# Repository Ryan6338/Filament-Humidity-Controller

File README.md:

# ESPHome Filament Humidity Controller (P/N 000001)
## Overview
This project is for an ESPHome-based 3D printer filament box. The purpose of the PCB is to automatically control a fan which will drive air through dessicant in a 3D printer filament drybox. Using ESPHome allows for easy configuration & automation customization through ESPHome and Home Assistant. It also allows for notifications to be configured when the dessicant has been depleted. The PCB is powered from a USB-C port requiring a 5V, 1A capable USB source. The USB port can be used for flashing the onboard ESP, although after ESPHome firmware has been installed, over the air updates can be used instead.

## File Layout
### [KiCAD](KiCAD/)
The KiCAD folder contains the entire KiCAD project. This can be used to modify the board.
### [Manufacturing Documents](Manufacturing%20Documents/)
The manufacturing documents contains all output files of the KiCAD project. These files fully define the finished PCB. The main document is 000001.pdf. This file has notes defining the other files.
### [Calculations](Calculations/)
Calculations & design criteria can be found in the calculations folder. SMath (.sm) files are used to generate the output files in this folder (.pdf).
### [Simulations](Simulations/)
The simulations folder contains LTSpice simulations generated during the project.
## Board Architecture
A block diagram of the board architecture is pictured below. Each block in the diagram is described in this section.

### USB-C Connector
The board takes in power from the USB-C connector and runs it to both a 12V boost converter and 3.3V linear regulator. The CC pins are used by the upstream device to communicate how much power can be supplied.
### 12V Boost Converter
The 12V boost converter receives 5V (4.75-5.25V) from the USB-C connector & converts it into 12V for the fan. The boost converter is only active when the enable signal is triggered by the ESP32.
### 3.3V Linear Regulator
The 3.3V linear regulator receives 5V from the USB-C connector and regulates it to 3.3V for the humidity sensor & ESP32.
### Humidity Sensor
The humidity sensor receives 3.3V from the linear regulator & is an I2C slave device on the I2C bus connected to the ESP32.
### ESP32
The ESP32 runs ESPHome firmware with a driver to perform fan control with speed feedback & to receive humidity sensor data. Using the custom humidity sensor & fan drivers, the firmware for the ESP32 can be generated using a standard ESPHome yaml file. The ESP32 interfaces with an ESPHome server allowing for easy configuration of control parameters. Upon power on, the ESP32 reads the voltage of the CC pins to ensure adequate power is available from the USB supply prior to enabling the boost converter.
### Fan Connector
The fan connector is a standard 4-Pin computer fan connector which can be used with any 12V computer fan which has a maximum current draw of 200mA or less.
## TODO
1. Write custom ESPHome driver.
2. Create example yaml for ESPHome using custom driver.
3. Design PCB bracket, fan housing & dessicant holder.
## Future Improvements
To make this product consumer-ready, the following improvements should be considered:
1. Add fuse to 5V input.
2. Add ESD protection on USB & fan connectors.

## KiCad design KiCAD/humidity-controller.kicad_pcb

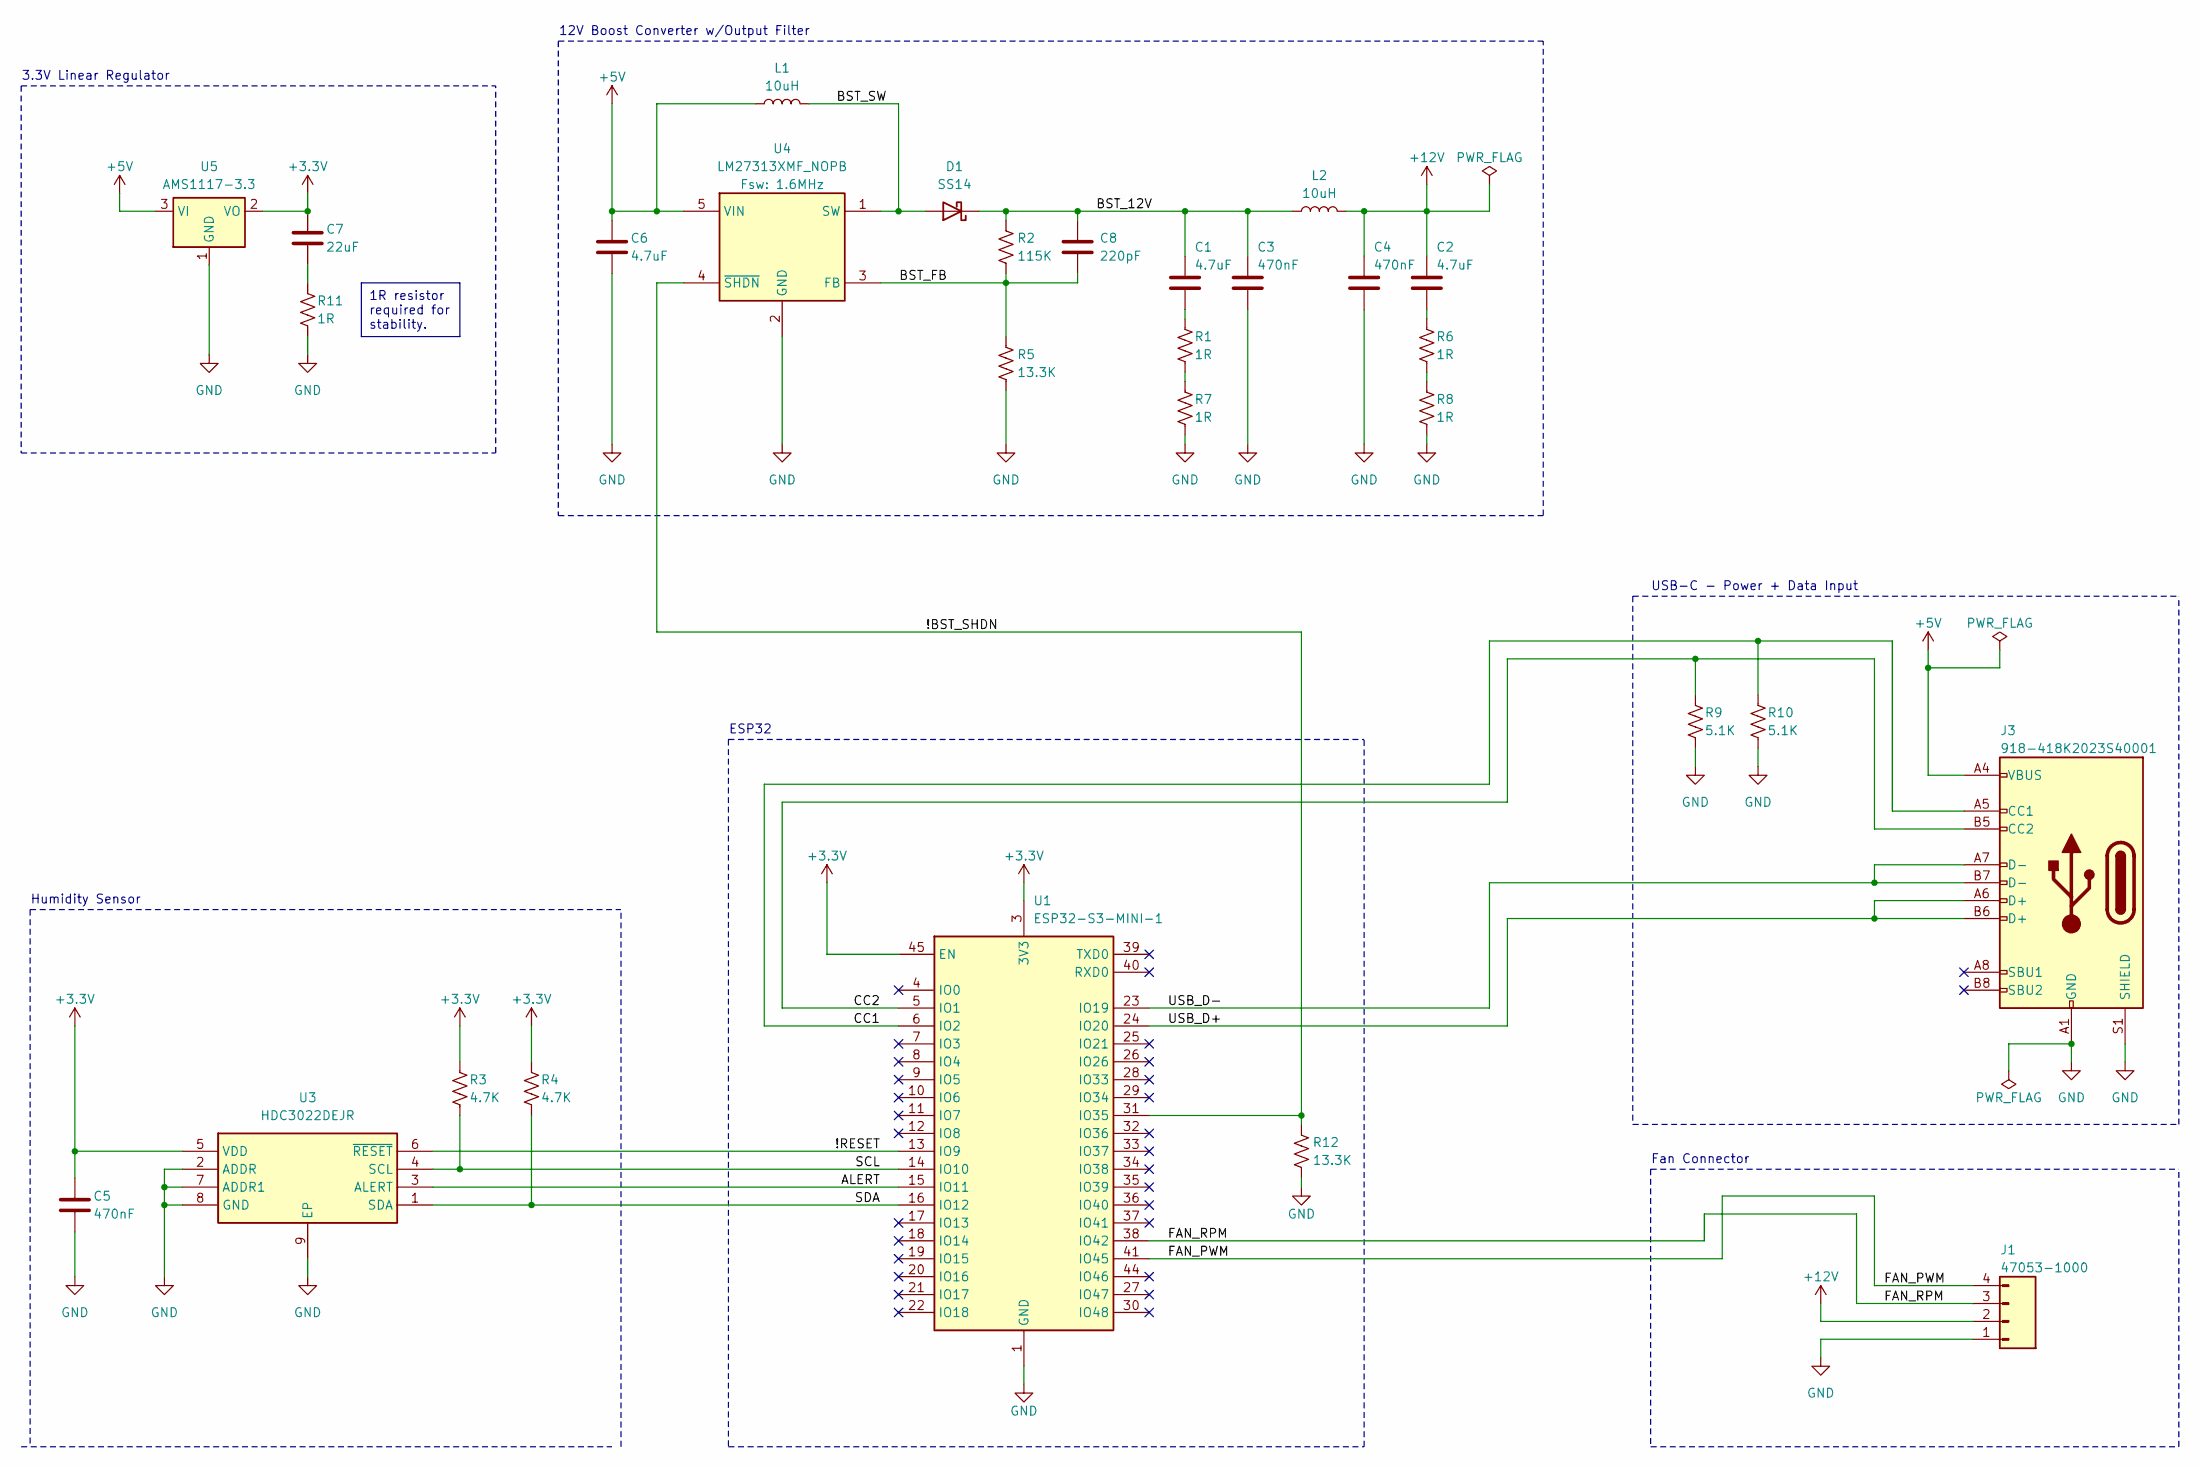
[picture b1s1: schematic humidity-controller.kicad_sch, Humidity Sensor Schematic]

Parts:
C1, C2, C6: 4.7uF; C_1206_3216Metric; MPN 1206B475K500NT; JLCPCB Part # C29823
C3, C4, C5: 470nF; C_0603_1608Metric; MPN CL10B474KA8NNNC; JLCPCB Part # C1623
C7: 22uF; C_0603_1608Metric; MPN CL10A226MQ8NRNC; JLCPCB Part # C59461
C8: 220pF; C_0402_1005Metric; MPN 0402B221K500NT; JLCPCB Part # C1530
D1: SS14; D_SMA; MPN MDD(Microdiode Semiconductor); JLCPCB Part # C2480
J1: Conn_01x04_Pin; 470531000; MPN 47053-1000; JLCPCB Part # C240840
J3: 918-418K2023S40001; USB_C_Receptacle_GCT_USB4105-xx-A_16P_TopMnt_Horizontal; MPN 918-418K2023S40001; JLCPCB Part # C167321
L1, L2: 10uH; L_Sunlord_SWPA3015S; MPN SWPA3015S100MT; JLCPCB Part # C45403
R1, R6, R7, R8, R11: 1R; C_0603_1608Metric; MPN 0603WAF100KT5E; JLCPCB Part # C22936
R2: 115K; R_0402_1005Metric; MPN 0402WGF1153TCE; JLCPCB Part # C25747
R3, R4: 4.7K; R_0402_1005Metric; MPN 0402WGF4701TCE; JLCPCB Part # C25900
R5, R12: 13.3K; R_0402_1005Metric; MPN 0402WGF1332TCE; JLCPCB Part # C122547
R9, R10: 5.1K; R_0402_1005Metric; MPN 0402WGF5101TCE; JLCPCB Part # C25905
U1: ESP32-S3-MINI-1; ESP32-S2-MINI-1; MPN ESP32-S3-MINI-1-N8; JLCPCB Part # C2913206
U3: HDC3022DEJR; SON50P250X250X80-9N-D; MPN HDC3022DEJR; JLCPCB Part # C7472806
U4: LM27313XMF_NOPB; SOT95P280X145-5N; MPN LM27313XMF/NOPB; JLCPCB Part # C32355
U5: AMS1117-3.3; SOT-223-3_TabPin2; MPN AMS1117-3.3; JLCPCB Part # C6186

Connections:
+3.3V: C5.1, C7.1, R3.1, R4.1, U1.3 (3V3), U1.45 (EN), U3.5 (VDD), U5.2 (VO)
+5V: C6.1, J3.A4 (VBUS), J3.A9 (VBUS), J3.B4 (VBUS), J3.B9 (VBUS), L1.1, U4.5 (VIN), U5.3 (VI)
+12V: C2.1, C4.1, J1.2, L2.2
/!BST_SHDN: R12.1, U1.31 (IO35), U4.4 (~SHDN)
/!RESET: U1.13 (IO9), U3.6 (~RESET)
/ALERT: U1.15 (IO11), U3.3 (ALERT)
/BST_12V: C1.1, C3.1, C8.1, D1.1 (K), L2.1, R2.1
/BST_FB: C8.2, R2.2, R5.1, U4.3 (FB)
/BST_SW: D1.2 (A), L1.2, U4.1 (SW)
/CC1: J3.A5 (CC1), R10.1, U1.6 (IO2)
/CC2: J3.B5 (CC2), R9.1, U1.5 (IO1)
/FAN_PWM: J1.4, U1.41 (IO45)
/FAN_RPM: J1.3, U1.38 (IO42)
/SCL: R3.2, U1.14 (IO10), U3.4 (SCL)
/SDA: R4.2, U1.16 (IO12), U3.1 (SDA)
/USB_D+: J3.A6 (D+), J3.B6 (D+), U1.24 (IO20)
/USB_D-: J3.A7 (D-), J3.B7 (D-), U1.23 (IO19)
GND: C3.2, C4.2, C5.2, C6.2, J1.1, J3.A1 (GND), J3.A12 (GND), J3.B1 (GND), J3.B12 (GND), J3.S1 (SHIELD), R5.2, R7.1, R8.1, R9.2, R10.2, R11.1, R12.2, U1.1 (GND), U1.2 (GND), U1.42 (GND), U1.43 (GND), U1.46 (GND), U1.47 (GND), U1.48 (GND), U1.49 (GND), U1.50 (GND), U1.51 (GND), U1.52 (GND), U1.53 (GND), U1.54 (GND), U1.55 (GND), U1.56 (GND), U1.57 (GND), U1.58 (GND), U1.59 (GND), U1.60 (GND), U1.61 (GND), U1.62 (GND), U1.63 (GND), U1.64 (GND), U1.65 (GND), U3.2 (ADDR), U3.7 (ADDR1), U3.8 (GND), U3.9 (EP), U4.2 (GND), U5.1 (GND)
unnamed: C1.2, R1.2
unnamed: C2.2, R6.2
unnamed: C7.2, R11.2
unnamed: R1.1, R7.2
unnamed: R6.1, R8.2

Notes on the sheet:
1R resistor required for stability.
Humidity Sensor
3.3V Linear Regulator
USB-C - Power + Data Input
ESP32
Fan Connector
12V Boost Converter w/Output Filter

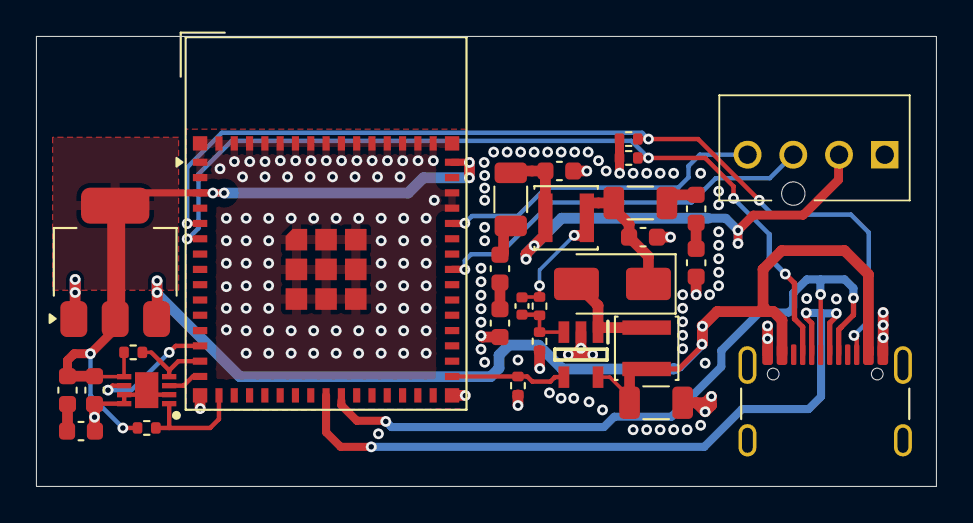
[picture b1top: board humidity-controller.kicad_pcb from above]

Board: 4 copper layers, 50.0 x 25.0 mm, 29 parts (0 on the bottom side), 23 nets.

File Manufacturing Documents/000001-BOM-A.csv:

Reference	Value	Qty	MF	MPN	Description	JLCPCB Part #
C1,C2,C6	4.7uF	3	FH (Guangdong Fenghua Advanced Tech)	1206B475K500NT	MLCC 4.7uF X7R 50V 1206	C29823
C3,C4,C5	470nF	3	Samsung Electro-Mechanics	CL10B474KA8NNNC	MLCC 470nF 25V X7R 0603	C1623
C7	22uF	1	Samsung Electro-Mechanics	CL10A226MQ8NRNC	MLCC 4.7uF X5R 6.3V 0603	C59461
C8	220pF	1	FH (Guangdong Fenghua Advanced Tech)	0402B221K500NT	MLCC 220pF X7R 50V 0402	C1530
D1	SS14	1	SS14	 MDD(Microdiode Semiconductor)	40V 1A Schottky Diode, SMA	C2480
J1	Conn_01x04_Pin	1	Molex	47053-1000	KK 254 Vertical Header, with Friction Lock, 4 Circuits	C240840
J3	918-418K2023S40001	1	Jing	918-418K2023S40001	USB 2.0-only 16P Type-C Receptacle connector	C167321
L1,L2	10uH	2	Sunlord	SWPA3015S100MT	Inductor 10uH 1.2A Isat	C45403
R1,R6,R7,R8,R11	1R	5	UNI-ROYAL(Uniroyal Elec)	0603WAF100KT5E	Resistor 1R 0603	C22936
R2	115K	1	UNI-ROYAL(Uniroyal Elec)	0402WGF1153TCE	Resistor 115K 0402	C25747
R3,R4	4.7K	2	UNI-ROYAL(Uniroyal Elec)	0402WGF4701TCE	Resistor 4.7K 0402	C25900
R5,R12	13.3K	2	UNI-ROYAL(Uniroyal Elec)	0402WGF1332TCE	Resistor 13.3K 0402	C122547
R9,R10	5.1K	2	UNI-ROYAL(Uniroyal Elec)	0402WGF5101TCE	Resistor 5.1K 0402	C25905
U1	ESP32-S3-MINI-1	1	Espressif Systems	ESP32-S3-MINI-1-N8	RF Module, ESP32-S3 SoC, Wi-Fi 802.11b/g/n, Bluetooth, BLE, 32-bit, 3.3V, SMD, onboard antenna	C2913206
U3	HDC3022DEJR	1	Texas Instruments	HDC3022DEJR	Board Mount Humidity Sensors 0.5% RH digital humidity sensor, 0.19% long-term drift, 400 nA, 4-sec response time, NIST traceable	C7472806
U4	LM27313XMF_NOPB	1	Texas Instruments	LM27313XMF/NOPB	1.6 MHz Boost Converter With 30V Internal FET Switch in SOT-23	C32355
U5	AMS1117-3.3	1	Advanced Monolithic Systems	AMS1117-3.3	1A Low Dropout regulator, positive, 3.3V fixed output, SOT-223	C6186

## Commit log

2025-02-10 Initial Release
2025-02-10 Added main file in manufacturing docs
2025-02-10 Update README.md
    Added rendering of PCB
2025-02-10 Update README.md
    Added description of CC pins
2025-02-10 Updated main drawing to improve component text readability
2025-02-12 Update README.md
    Added picture of actual PCB to readme.
2025-02-12 Added esphome configuration yaml enabling fan control. Humidity sensor reading needs to have a custom component developed.
